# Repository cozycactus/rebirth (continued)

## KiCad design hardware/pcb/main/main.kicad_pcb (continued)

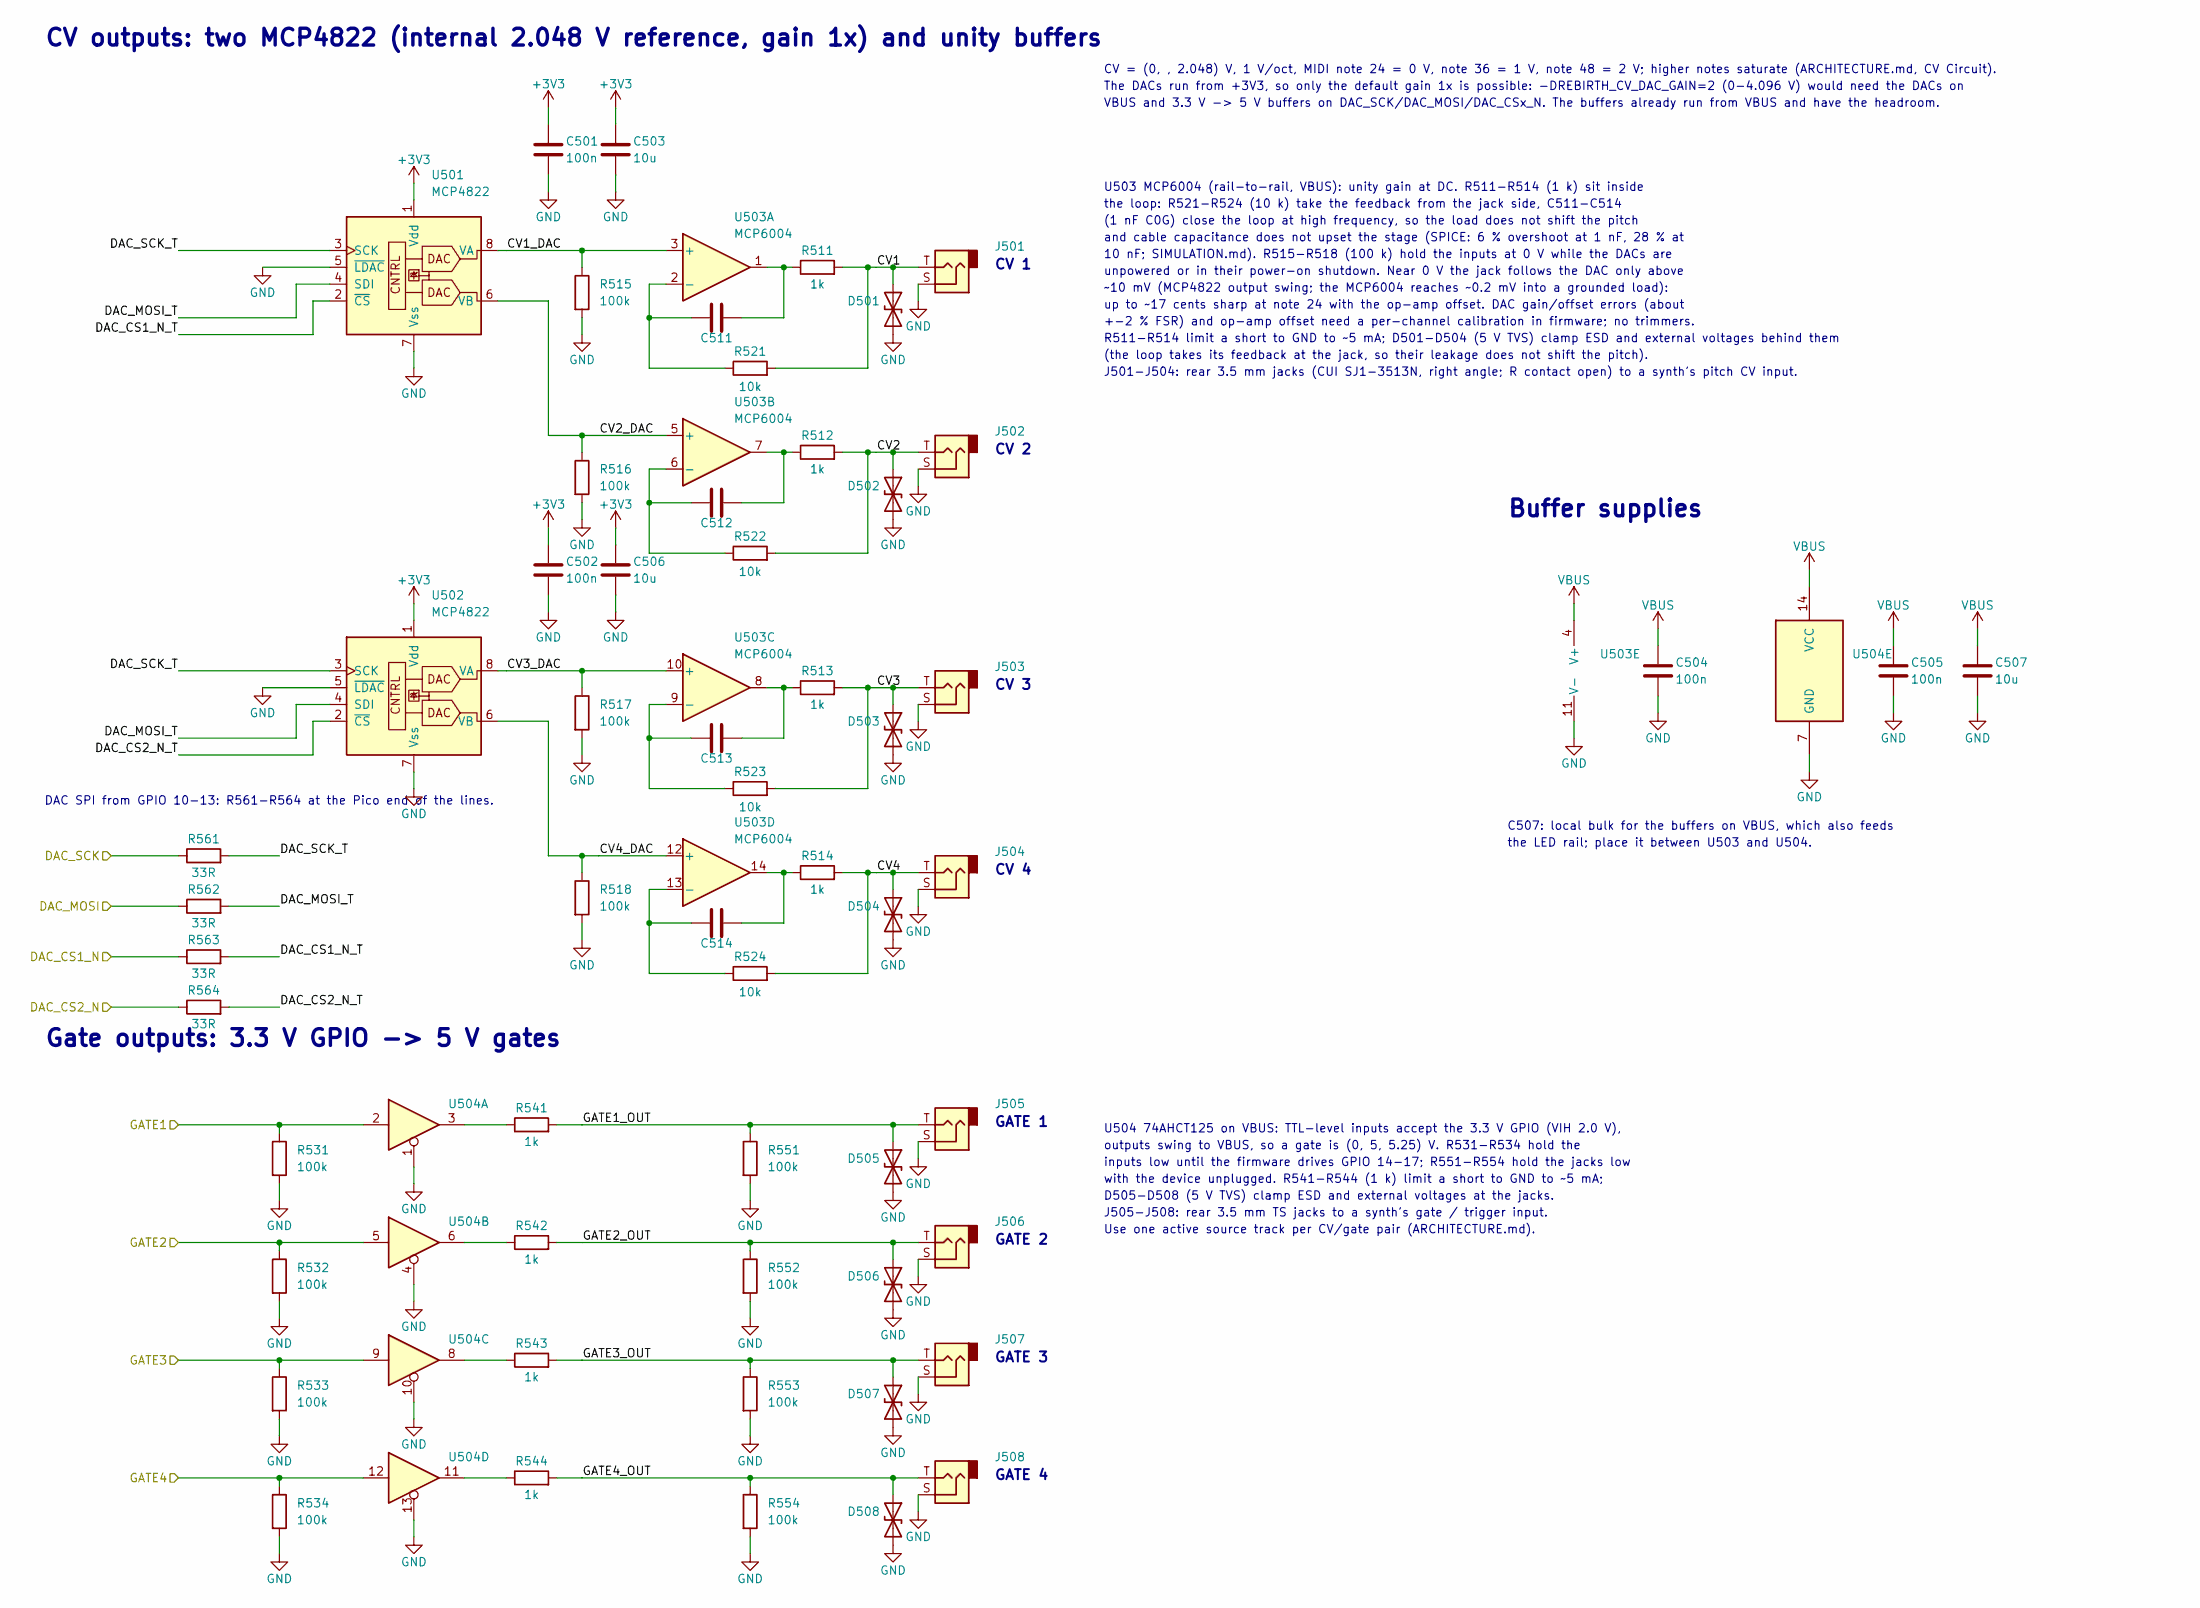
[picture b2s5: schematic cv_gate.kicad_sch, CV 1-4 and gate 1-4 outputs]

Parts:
C501, C502, C504, C505: 100n; C_0603_1608Metric
C503, C506, C507: 10u; C_0805_2012Metric
C511, C512, C513, C514: 1n C0G; C_0603_1608Metric
D501, D502, D503, D504, D505, D506, D507, D508: PESD5V0S1BA; D_SOD-323
J501, J502, J503, J504, J505, J506, J507, J508: 3.5mm TS; Jack_3.5mm_CUI_SJ1-3513N_Horizontal
R511, R512, R513, R514, R541, R542, R543, R544: 1k; R_0603_1608Metric
R515, R516, R517, R518, R531, R532, R533, R534, R551, R552, R553, R554: 100k; R_0603_1608Metric
R521, R522, R523, R524: 10k; R_0603_1608Metric
R561, R562, R563, R564: 33R; R_0603_1608Metric
U501, U502: MCP4822; SOIC-8_3.9x4.9mm_P1.27mm
U503: MCP6004; SOIC-14_3.9x8.7mm_P1.27mm
U504: 74AHCT125; SOIC-14_3.9x8.7mm_P1.27mm

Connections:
+3V3: C501.1, C502.1, C503.1, C506.1, U501.1 (Vdd), U502.1 (Vdd); also elsewhere on the board
/CV_Gate/CV1: D501.1 (A1), J501.T, R511.2, R521.2
/CV_Gate/CV1_DAC: R515.1, U501.8 (VA), U503.3 (+)
/CV_Gate/CV2: D502.1 (A1), J502.T, R512.2, R522.2
/CV_Gate/CV2_DAC: R516.1, U501.6 (VB), U503.5 (+)
/CV_Gate/CV3: D503.1 (A1), J503.T, R513.2, R523.2
/CV_Gate/CV3_DAC: R517.1, U502.8 (VA), U503.10 (+)
/CV_Gate/CV4: D504.1 (A1), J504.T, R514.2, R524.2
/CV_Gate/CV4_DAC: R518.1, U502.6 (VB), U503.12 (+)
/CV_Gate/DAC_CS1_N_T: R563.2, U501.2 (~CS)
/CV_Gate/DAC_CS2_N_T: R564.2, U502.2 (~CS)
/CV_Gate/DAC_MOSI_T: R562.2, U501.4 (SDI), U502.4 (SDI)
/CV_Gate/DAC_SCK_T: R561.2, U501.3 (SCK), U502.3 (SCK)
/CV_Gate/GATE1_OUT: D505.1 (A1), J505.T, R541.2, R551.1
/CV_Gate/GATE2_OUT: D506.1 (A1), J506.T, R542.2, R552.1
/CV_Gate/GATE3_OUT: D507.1 (A1), J507.T, R543.2, R553.1
/CV_Gate/GATE4_OUT: D508.1 (A1), J508.T, R544.2, R554.1
/DAC_CS1_N: R563.1; also elsewhere on the board
/DAC_CS2_N: R564.1; also elsewhere on the board
/DAC_MOSI: R562.1; also elsewhere on the board
/DAC_SCK: R561.1; also elsewhere on the board
/GATE1: R531.1, U504.2; also elsewhere on the board
/GATE2: R532.1, U504.5; also elsewhere on the board
/GATE3: R533.1, U504.9; also elsewhere on the board
/GATE4: R534.1, U504.12; also elsewhere on the board
GND: C501.2, C502.2, C503.2, C504.2, C505.2, C506.2, C507.2, D501.2 (A2), D502.2 (A2), D503.2 (A2), D504.2 (A2), D505.2 (A2), D506.2 (A2), D507.2 (A2), D508.2 (A2), J501.S, J502.S, J503.S, J504.S, J505.S, J506.S, J507.S, J508.S, R515.2, R516.2, R517.2, R518.2, R531.2, R532.2, R533.2, R534.2, R551.2, R552.2, R553.2, R554.2, U501.5 (~LDAC), U501.7 (Vss), U502.5 (~LDAC), U502.7 (Vss), U503.11 (V-), U504.1, U504.4, U504.7 (GND), U504.10, U504.13; also elsewhere on the board
unnamed: C511.2, R511.1, U503.1
unnamed: C512.2, R512.1, U503.7
unnamed: C513.2, R513.1, U503.8
unnamed: C514.2, R514.1, U503.14
unnamed: R541.1, U504.3
unnamed: R542.1, U504.6
unnamed: R543.1, U504.8
unnamed: R544.1, U504.11
unnamed: C511.1, R521.1, U503.2 (-)
unnamed: C512.1, R522.1, U503.6 (-)
unnamed: C513.1, R523.1, U503.9 (-)
unnamed: C514.1, R524.1, U503.13 (-)
VBUS: C504.1, C505.1, C507.1, U503.4 (V+), U504.14 (VCC); also elsewhere on the board

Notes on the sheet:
CV outputs: two MCP4822 (internal 2.048 V reference, gain 1x) and unity buffers
CV = (0, , 2.048) V, 1 V/oct, MIDI note 24 = 0 V, note 36 = 1 V, note 48 = 2 V; higher notes saturate (ARCHITECTURE.md, CV Circuit).
The DACs run from +3V3, so only the default gain 1x is possible: -DREBIRTH_CV_DAC_GAIN=2 (0-4.096 V) would need the DACs on
VBUS and 3.3 V -> 5 V buffers on DAC_SCK/DAC_MOSI/DAC_CSx_N. The buffers already run from VBUS and have the headroom.
DAC SPI from GPIO 10-13: R561-R564 at the Pico end of the lines.
CV 1
CV 2
CV 3
CV 4
U503 MCP6004 (rail-to-rail, VBUS): unity gain at DC. R511-R514 (1 k) sit inside
the loop: R521-R524 (10 k) take the feedback from the jack side, C511-C514
(1 nF C0G) close the loop at high frequency, so the load does not shift the pitch
and cable capacitance does not upset the stage (SPICE: 6 % overshoot at 1 nF, 28 % at
10 nF; SIMULATION.md). R515-R518 (100 k) hold the inputs at 0 V while the DACs are
unpowered or in their power-on shutdown. Near 0 V the jack follows the DAC only above
~10 mV (MCP4822 output swing; the MCP6004 reaches ~0.2 mV into a grounded load):
up to ~17 cents sharp at note 24 with the op-amp offset. DAC gain/offset errors (about
+-2 % FSR) and op-amp offset need a per-channel calibration in firmware; no trimmers.
R511-R514 limit a short to GND to ~5 mA; D501-D504 (5 V TVS) clamp ESD and external voltages behind them
(the loop takes its feedback at the jack, so their leakage does not shift the pitch).
J501-J504: rear 3.5 mm jacks (CUI SJ1-3513N, right angle; R contact open) to a synth's pitch CV input.
Gate outputs: 3.3 V GPIO -> 5 V gates
GATE 1
GATE 2
GATE 3
GATE 4
U504 74AHCT125 on VBUS: TTL-level inputs accept the 3.3 V GPIO (VIH 2.0 V),
outputs swing to VBUS, so a gate is (0, 5, 5.25) V. R531-R534 hold the
inputs low until the firmware drives GPIO 14-17; R551-R554 hold the jacks low
with the device unplugged. R541-R544 (1 k) limit a short to GND to ~5 mA;
D505-D508 (5 V TVS) clamp ESD and external voltages at the jacks.
J505-J508: rear 3.5 mm TS jacks to a synth's gate / trigger input.
Use one active source track per CV/gate pair (ARCHITECTURE.md).
Buffer supplies
C507: local bulk for the buffers on VBUS, which also feeds
the LED rail; place it between U503 and U504.

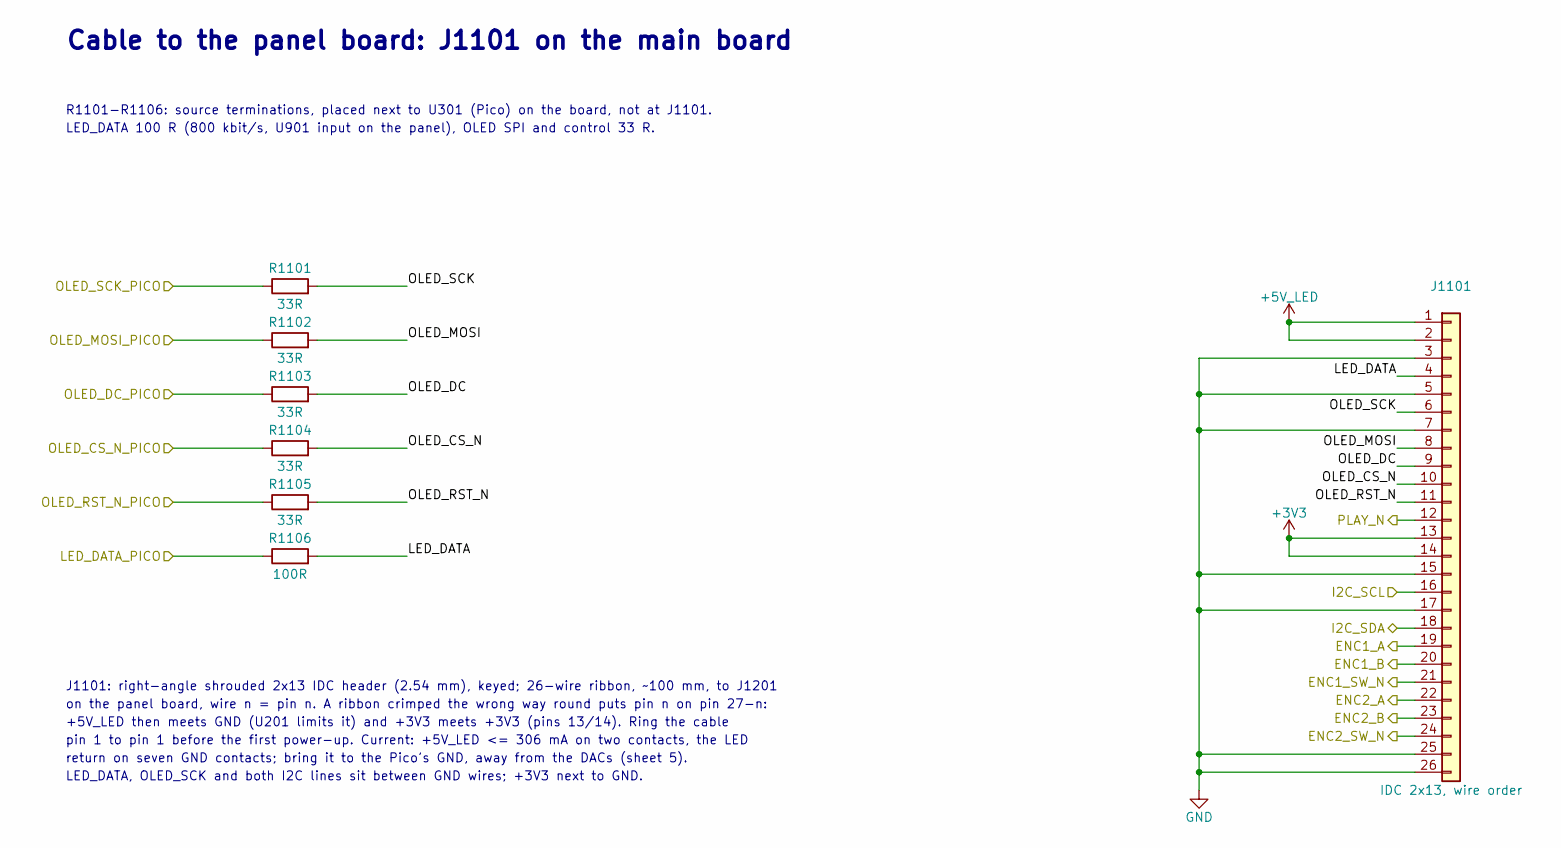
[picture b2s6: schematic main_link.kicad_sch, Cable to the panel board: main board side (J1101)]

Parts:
J1101: IDC 2x13, wire order; IDC-Header_2x13_P2.54mm_Horizontal
R1101, R1102, R1103, R1104, R1105: 33R; R_0603_1608Metric
R1106: 100R; R_0603_1608Metric

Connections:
+3V3: J1101.13, J1101.14; also elsewhere on the board
+5V_LED: J1101.1, J1101.2; also elsewhere on the board
/ENC1_A: J1101.19; also elsewhere on the board
/ENC1_B: J1101.20; also elsewhere on the board
/ENC1_SW_N: J1101.21; also elsewhere on the board
/ENC2_A: J1101.22; also elsewhere on the board
/ENC2_B: J1101.23; also elsewhere on the board
/ENC2_SW_N: J1101.24; also elsewhere on the board
/I2C_SCL: J1101.16; also elsewhere on the board
/I2C_SDA: J1101.18; also elsewhere on the board
/LED_DATA_PICO: R1106.1; also elsewhere on the board
/Main_link/LED_DATA: J1101.4, R1106.2
/Main_link/OLED_CS_N: J1101.10, R1104.2
/Main_link/OLED_DC: J1101.9, R1103.2
/Main_link/OLED_MOSI: J1101.8, R1102.2
/Main_link/OLED_RST_N: J1101.11, R1105.2
/Main_link/OLED_SCK: J1101.6, R1101.2
/OLED_CS_N_PICO: R1104.1; also elsewhere on the board
/OLED_DC_PICO: R1103.1; also elsewhere on the board
/OLED_MOSI_PICO: R1102.1; also elsewhere on the board
/OLED_RST_N_PICO: R1105.1; also elsewhere on the board
/OLED_SCK_PICO: R1101.1; also elsewhere on the board
/PLAY_N: J1101.12; also elsewhere on the board
GND: J1101.3, J1101.5, J1101.7, J1101.15, J1101.17, J1101.25, J1101.26; also elsewhere on the board

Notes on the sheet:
Cable to the panel board: J1101 on the main board
R1101-R1106: source terminations, placed next to U301 (Pico) on the board, not at J1101.
LED_DATA 100 R (800 kbit/s, U901 input on the panel), OLED SPI and control 33 R.
J1101: right-angle shrouded 2x13 IDC header (2.54 mm), keyed; 26-wire ribbon, ~100 mm, to J1201
on the panel board, wire n = pin n. A ribbon crimped the wrong way round puts pin n on pin 27-n:
+5V_LED then meets GND (U201 limits it) and +3V3 meets +3V3 (pins 13/14). Ring the cable
pin 1 to pin 1 before the first power-up. Current: +5V_LED <= 306 mA on two contacts, the LED
return on seven GND contacts; bring it to the Pico's GND, away from the DACs (sheet 5).
LED_DATA, OLED_SCK and both I2C lines sit between GND wires; +3V3 next to GND.

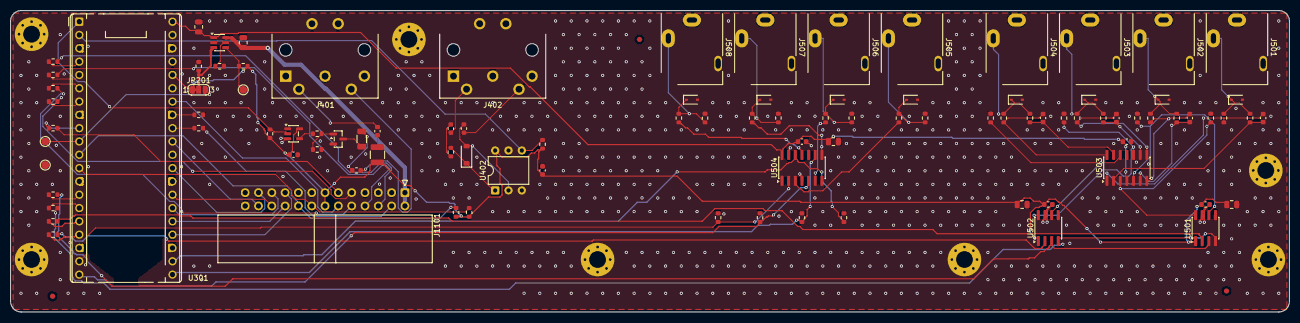
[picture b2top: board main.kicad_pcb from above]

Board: 2 copper layers, 244.0 x 57.5 mm, 109 parts (0 on the bottom side), 80 nets.

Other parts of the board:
FID1, FID2, FID3: Fiducial_1mm_Mask2mm
H1, H2, H3, H4, H5, H6, H7: MountingHole_3.2mm_M3_Pad_Via

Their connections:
GND: H1.1, H2.1, H3.1, H4.1, H5.1, H6.1, H7.1; also elsewhere on the board

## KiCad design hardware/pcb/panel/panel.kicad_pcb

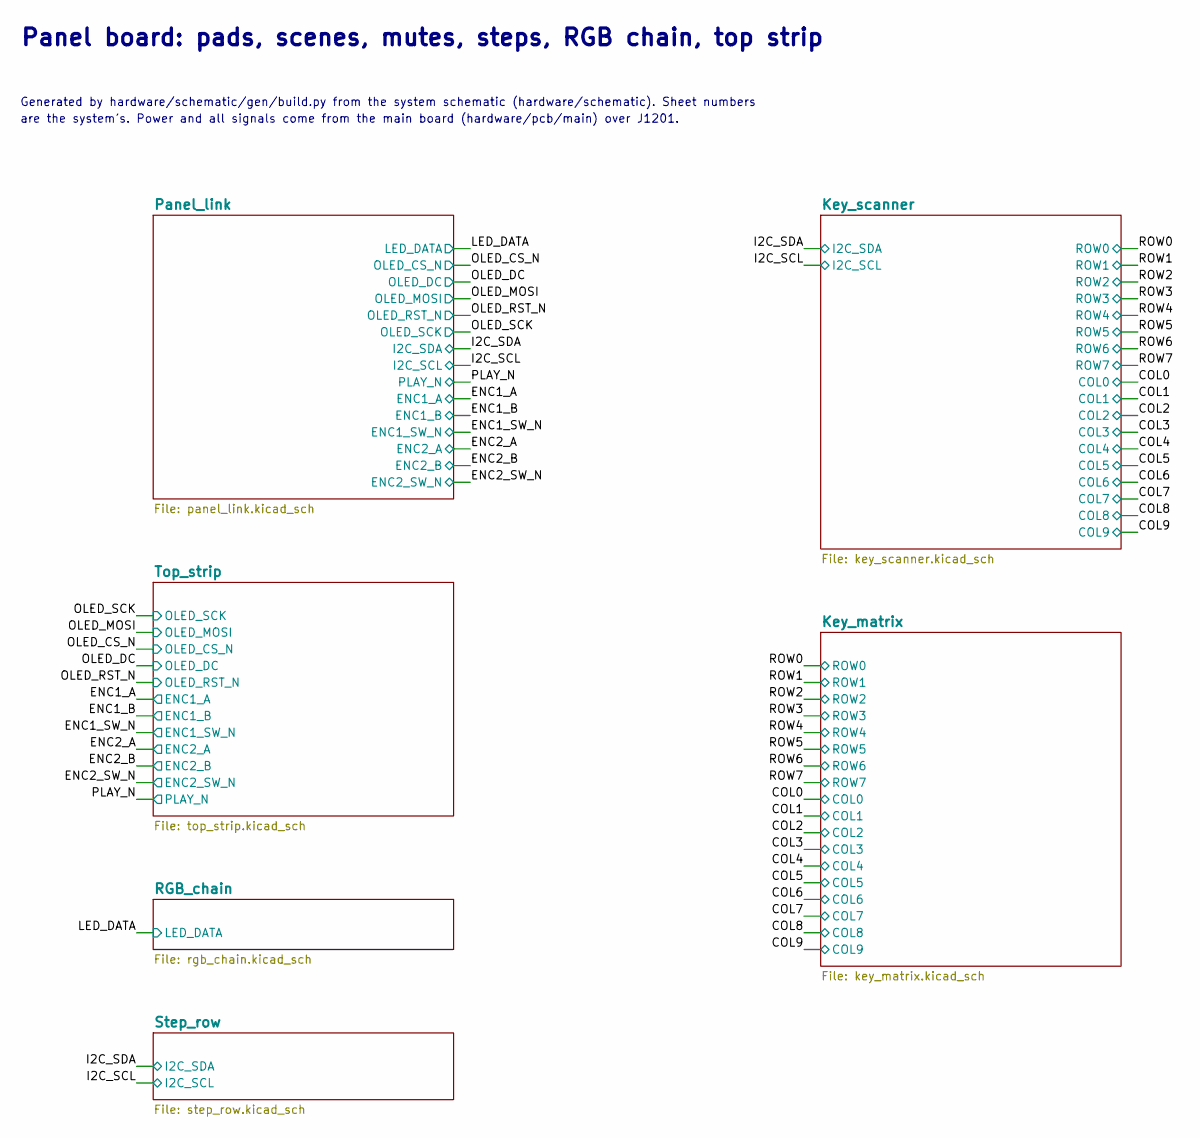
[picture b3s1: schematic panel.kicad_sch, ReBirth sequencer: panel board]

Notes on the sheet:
Panel board: pads, scenes, mutes, steps, RGB chain, top strip
Generated by hardware/schematic/gen/build.py from the system schematic (hardware/schematic). Sheet numbers
are the system's. Power and all signals come from the main board (hardware/pcb/main) over J1201.

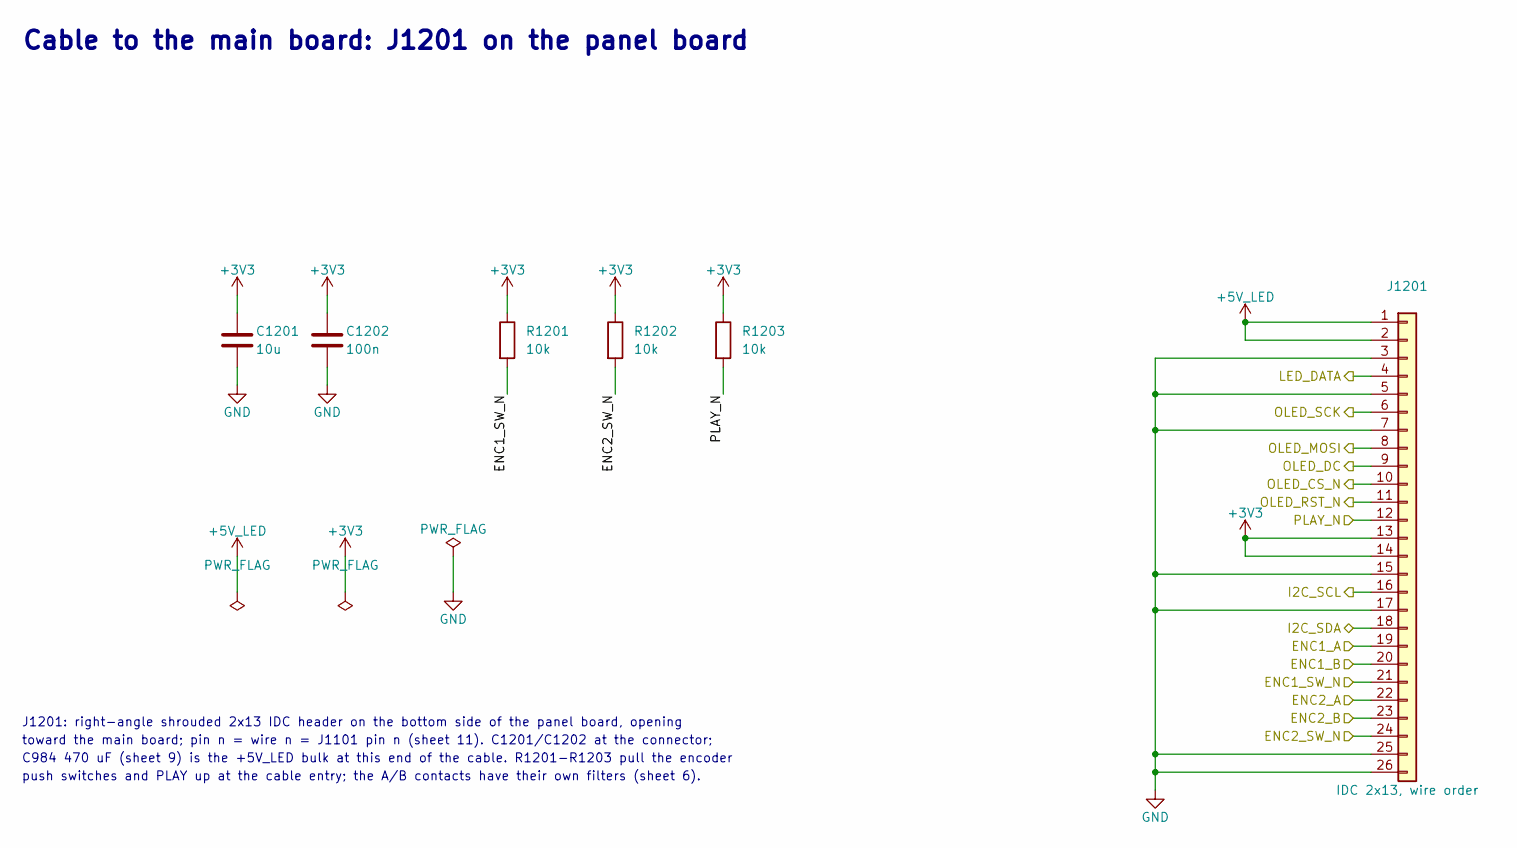
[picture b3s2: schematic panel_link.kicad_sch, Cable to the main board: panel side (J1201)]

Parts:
C1201: 10u; C_0805_2012Metric
C1202: 100n; C_0603_1608Metric
J1201: IDC 2x13, wire order; IDC-Header_2x13_P2.54mm_Horizontal
R1201, R1202, R1203: 10k; R_0603_1608Metric

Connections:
+3V3: C1201.1, C1202.1, J1201.13, J1201.14, R1201.1, R1202.1, R1203.1; also elsewhere on the board
+5V_LED: J1201.1, J1201.2; also elsewhere on the board
/ENC1_A: J1201.19; also elsewhere on the board
/ENC1_B: J1201.20; also elsewhere on the board
/ENC1_SW_N: J1201.21, R1201.2; also elsewhere on the board
/ENC2_A: J1201.22; also elsewhere on the board
/ENC2_B: J1201.23; also elsewhere on the board
/ENC2_SW_N: J1201.24, R1202.2; also elsewhere on the board
/I2C_SCL: J1201.16; also elsewhere on the board
/I2C_SDA: J1201.18; also elsewhere on the board
/LED_DATA: J1201.4; also elsewhere on the board
/OLED_CS_N: J1201.10; also elsewhere on the board
/OLED_DC: J1201.9; also elsewhere on the board
/OLED_MOSI: J1201.8; also elsewhere on the board
/OLED_RST_N: J1201.11; also elsewhere on the board
/OLED_SCK: J1201.6; also elsewhere on the board
/PLAY_N: J1201.12, R1203.2; also elsewhere on the board
GND: C1201.2, C1202.2, J1201.3, J1201.5, J1201.7, J1201.15, J1201.17, J1201.25, J1201.26; also elsewhere on the board

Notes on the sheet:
Cable to the main board: J1201 on the panel board
J1201: right-angle shrouded 2x13 IDC header on the bottom side of the panel board, opening
toward the main board; pin n = wire n = J1101 pin n (sheet 11). C1201/C1202 at the connector;
C984 470 uF (sheet 9) is the +5V_LED bulk at this end of the cable. R1201-R1203 pull the encoder
push switches and PLAY up at the cable entry; the A/B contacts have their own filters (sheet 6).

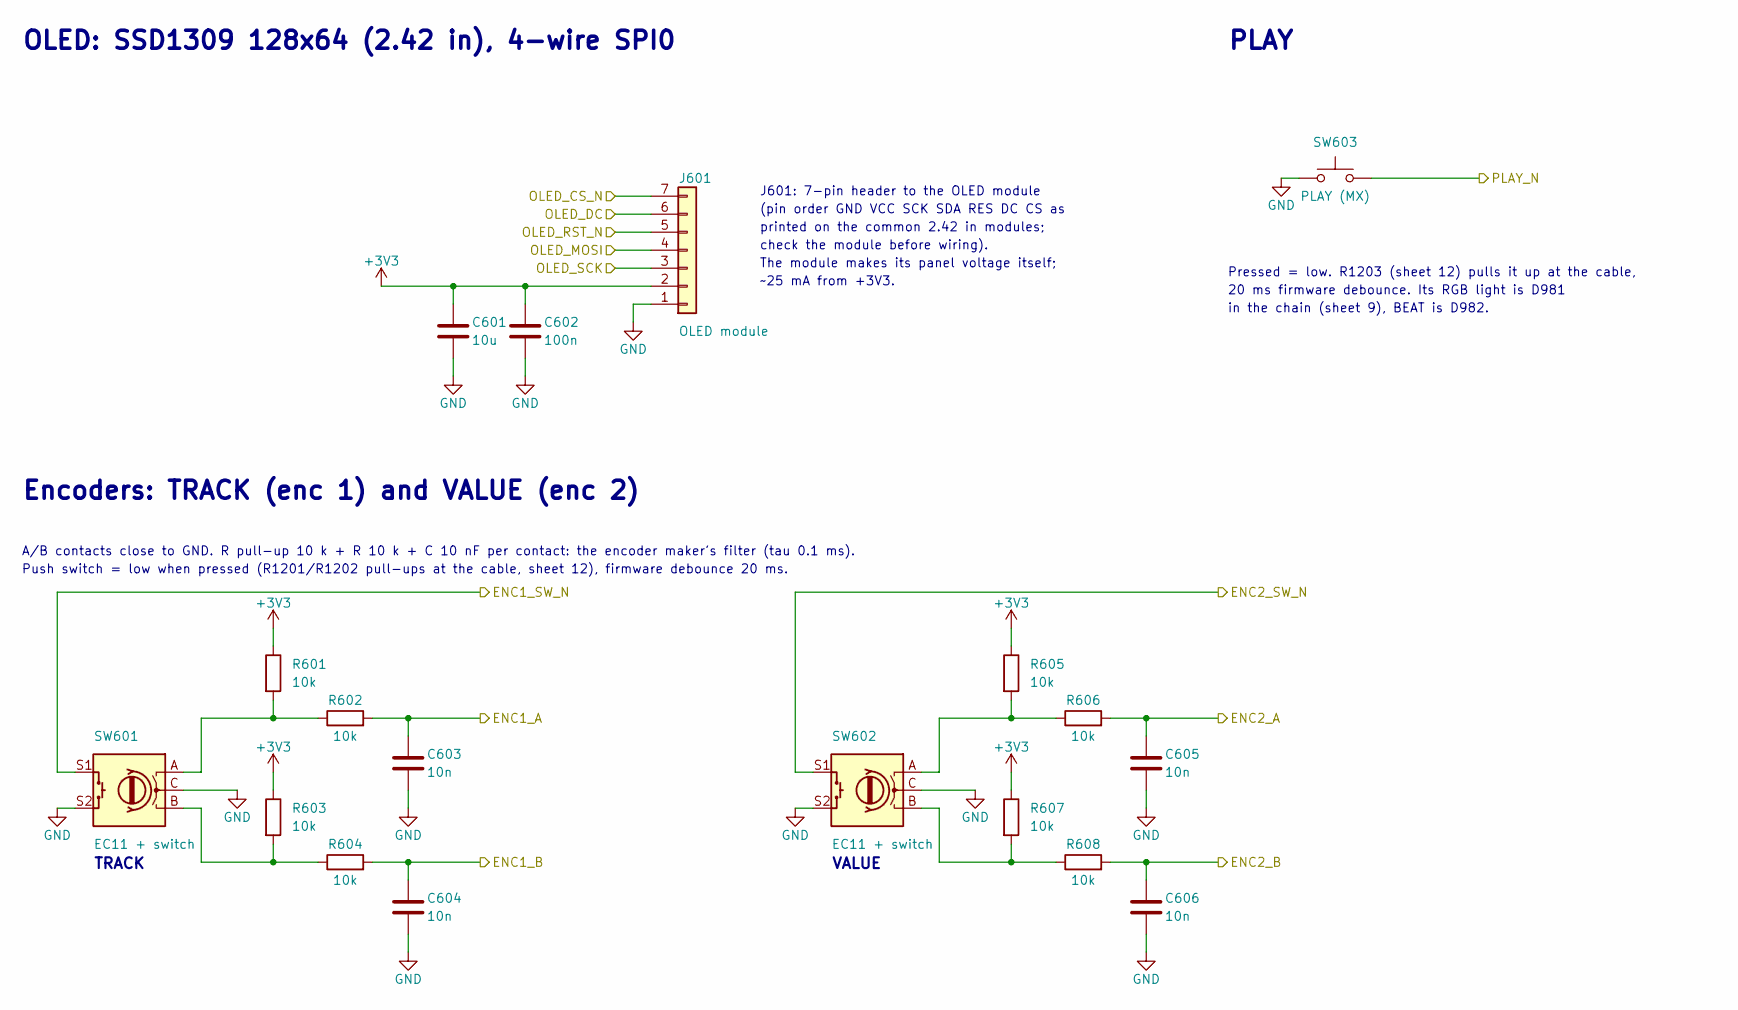
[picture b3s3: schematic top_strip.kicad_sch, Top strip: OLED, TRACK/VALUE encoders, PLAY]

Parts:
C601: 10u; C_0805_2012Metric
C602: 100n; C_0603_1608Metric
C603, C604, C605, C606: 10n; C_0603_1608Metric
J601: OLED module; PinSocket_1x07_P2.54mm_Vertical
R601, R602, R603, R604, R605, R606, R607, R608: 10k; R_0603_1608Metric
SW601, SW602: EC11 + switch; RotaryEncoder_Alps_EC11E-Switch_Vertical_H20mm
SW603: PLAY (MX); SW_Cherry_MX_1.00u_PCB

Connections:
+3V3: C601.1, C602.1, J601.2, R601.1, R603.1, R605.1, R607.1; also elsewhere on the board
/ENC1_A: C603.1, R602.2; also elsewhere on the board
/ENC1_B: C604.1, R604.2; also elsewhere on the board
/ENC1_SW_N: SW601.S1; also elsewhere on the board
/ENC2_A: C605.1, R606.2; also elsewhere on the board
/ENC2_B: C606.1, R608.2; also elsewhere on the board
/ENC2_SW_N: SW602.S1; also elsewhere on the board
/OLED_CS_N: J601.7; also elsewhere on the board
/OLED_DC: J601.6; also elsewhere on the board
/OLED_MOSI: J601.4; also elsewhere on the board
/OLED_RST_N: J601.5; also elsewhere on the board
/OLED_SCK: J601.3; also elsewhere on the board
/PLAY_N: SW603.2; also elsewhere on the board
GND: C601.2, C602.2, C603.2, C604.2, C605.2, C606.2, J601.1, SW601.C, SW601.S2, SW602.C, SW602.S2, SW603.1; also elsewhere on the board
unnamed: R601.2, R602.1, SW601.A
unnamed: R603.2, R604.1, SW601.B
unnamed: R605.2, R606.1, SW602.A
unnamed: R607.2, R608.1, SW602.B

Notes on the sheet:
OLED: SSD1309 128x64 (2.42 in), 4-wire SPI0
J601: 7-pin header to the OLED module
(pin order GND VCC SCK SDA RES DC CS as
printed on the common 2.42 in modules;
check the module before wiring).
The module makes its panel voltage itself;
~25 mA from +3V3.
PLAY
Pressed = low. R1203 (sheet 12) pulls it up at the cable,
20 ms firmware debounce. Its RGB light is D981
in the chain (sheet 9), BEAT is D982.
Encoders: TRACK (enc 1) and VALUE (enc 2)
A/B contacts close to GND. R pull-up 10 k + R 10 k + C 10 nF per contact: the encoder maker's filter (tau 0.1 ms).
Push switch = low when pressed (R1201/R1202 pull-ups at the cable, sheet 12), firmware debounce 20 ms.
TRACK
VALUE
